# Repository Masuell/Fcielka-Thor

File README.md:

# Fcielka-Thor

This repository contains programms which were used for diploma thesis about [Varroa Destructor detection on honey bees with using narrow spectra of illumination](https://www.vut.cz/studenti/zav-prace/detail/167591).

The thesis focuses on the development of a system for detecting mites on bees using computer vision techniques and illumination with specific wavelengths. The wavelengths employed are 500 nm, corresponding to turquoise light, and 780 nm, corresponding to infrared light. Both classical image processing methods and deep learning approaches are utilized. The primary objective was to capture images of bees as they pass through a [Bee Health Monitor device](https://github.com/boortel/Bee-Health-Monitor) while being illuminated with a narrow spectrum of light. Another goal was to train models capable of reliably identifying mites on bees, thereby reducing the need for manual hive inspections. The developed models include the YOLOv11 object detection architecture and the U-net semantic segmentation architecture, both of which achieved satisfactory performance. A key remaining challenge is the accurate detection of mites located on the edges of bees, which may be addressed by simultaneous illumination with both wavelengths.

You can find [the created dataset here](https://www.kaggle.com/datasets/masuel/bee-hyperspectral-dataset). It consists of photos of bees, mites and bees with mites before and after fumigation treatment. All categories is illuminated by IR, turquoise or white light. Besides that, there is also annotation for semantic segmentation (1 color channel = 1 category) and object detector (YOLO format) there. 

In Best_illumination_ratio folder is code to determine the best illumination ratio (if both colors are turned on).

In CameraCalibration folder is Calibrator module for Bee Health Monitor device.

ImitationOfBothColorsIllumination folder is code to simulate photos with both illumination. The pictures are composed of photos under IR and turquoise with linear regression.

As detection models were used [U-net semantic segmentation architecture](https://github.com/milesial/Pytorch-UNet) and [YOLOv11](https://github.com/ultralytics/ultralytics) object detection architecture.

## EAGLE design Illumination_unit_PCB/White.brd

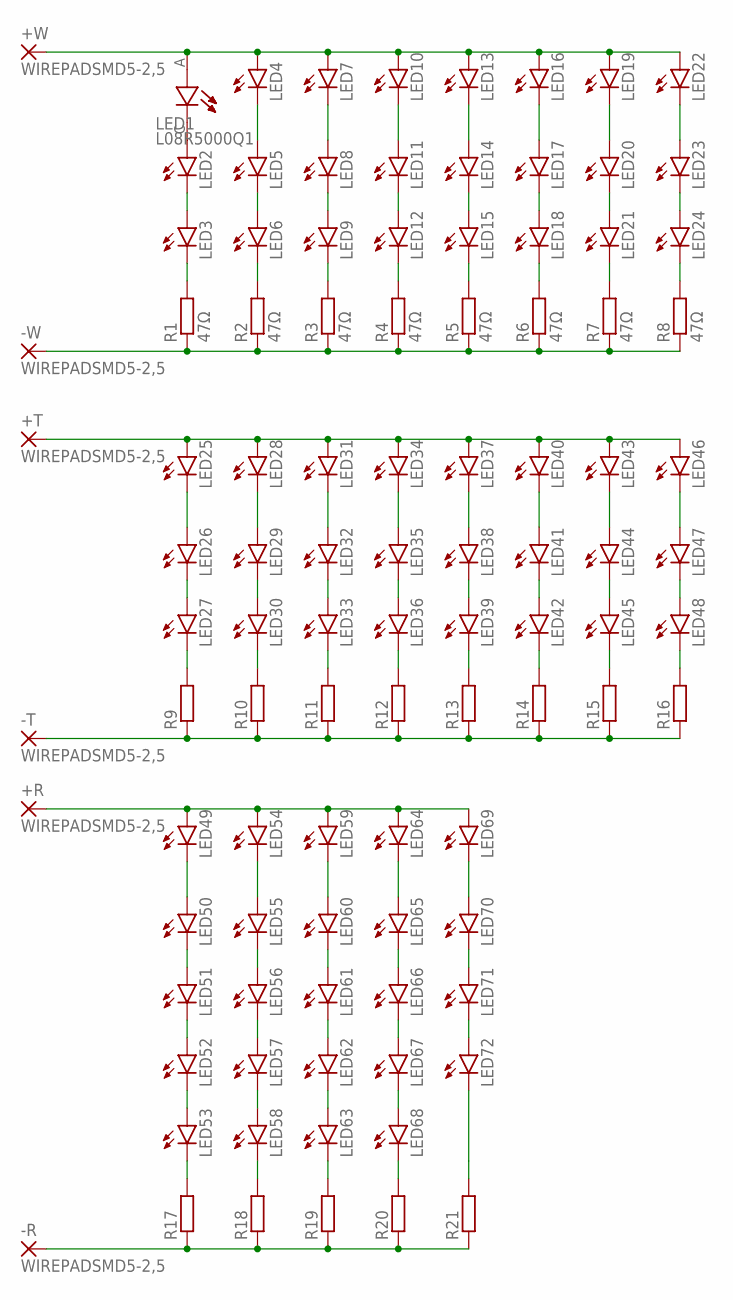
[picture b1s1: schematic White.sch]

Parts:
+R: WIREPADSMD5-2,5; 5-2,5
+T: WIREPADSMD5-2,5; 5-2,5
+W: WIREPADSMD5-2,5; 5-2,5
-R: WIREPADSMD5-2,5; 5-2,5
-T: WIREPADSMD5-2,5; 5-2,5
-W: WIREPADSMD5-2,5; 5-2,5
LED1: L08R5000Q1; LEDRD254W57D500H1070
LED2, LED3, LED4, LED5, LED6, LED7, LED8, LED9, LED10, LED11, LED12, LED13, LED14, LED15, LED16, LED17, LED18, LED19, LED20, LED21, LED22, LED23, LED24, LED25, LED26, LED27, LED28, LED29, LED30, LED31, LED32, LED33, LED34, LED35, LED36, LED37, LED38, LED39, LED40, LED41, LED42, LED43, LED44, LED45, LED46, LED47, LED48, LED49, LED50, LED51, LED52, LED53, LED54, LED55, LED56, LED57, LED58, LED59, LED60, LED61, LED62, LED63, LED64, LED65, LED66, LED67, LED68, LED69, LED70, LED71, LED72: LED5MM
R1, R2, R3, R4, R5, R6, R7, R8: 47Ω; 0411/15
R9, R10, R11, R12, R13, R14, R15, R16, R17, R18, R19, R20, R21: R-EU_0207/12; 0207/12

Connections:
unnamed: LED1.C, LED2.A
unnamed: LED2.K (C), LED3.A
unnamed: LED3.K (C), R1.2
unnamed: +W.1, LED1.A, LED4.A, LED7.A, LED10.A, LED13.A, LED16.A, LED19.A, LED22.A
unnamed: LED25.K (C), LED26.A
unnamed: LED4.K (C), LED5.A
unnamed: LED5.K (C), LED6.A
unnamed: LED6.K (C), R2.2
unnamed: LED7.K (C), LED8.A
unnamed: LED8.K (C), LED9.A
unnamed: LED9.K (C), R3.2
unnamed: LED10.K (C), LED11.A
unnamed: LED11.K (C), LED12.A
unnamed: LED12.K (C), R4.2
unnamed: LED22.K (C), LED23.A
unnamed: LED13.K (C), LED14.A
unnamed: LED14.K (C), LED15.A
unnamed: LED15.K (C), R5.2
unnamed: LED16.K (C), LED17.A
unnamed: LED17.K (C), LED18.A
unnamed: LED18.K (C), R6.2
unnamed: LED19.K (C), LED20.A
unnamed: LED20.K (C), LED21.A
unnamed: LED21.K (C), R7.2
unnamed: LED23.K (C), LED24.A
unnamed: LED24.K (C), R8.2
unnamed: LED26.K (C), LED27.A
unnamed: LED27.K (C), R9.2
unnamed: +T.1, LED25.A, LED28.A, LED31.A, LED34.A, LED37.A, LED40.A, LED43.A, LED46.A
unnamed: LED28.K (C), LED29.A
unnamed: LED29.K (C), LED30.A
unnamed: LED30.K (C), R10.2
unnamed: LED31.K (C), LED32.A
unnamed: LED32.K (C), LED33.A
unnamed: -W.1, R1.1, R2.1, R3.1, R4.1, R5.1, R6.1, R7.1, R8.1
unnamed: LED33.K (C), R11.2
unnamed: LED34.K (C), LED35.A
unnamed: LED35.K (C), LED36.A
unnamed: LED36.K (C), R12.2
unnamed: LED37.K (C), LED38.A
unnamed: LED38.K (C), LED39.A
unnamed: LED39.K (C), R13.2
unnamed: LED40.K (C), LED41.A
unnamed: LED41.K (C), LED42.A
unnamed: LED42.K (C), R14.2
unnamed: LED43.K (C), LED44.A
unnamed: LED44.K (C), LED45.A
unnamed: LED45.K (C), R15.2
unnamed: -T.1, R9.1, R10.1, R11.1, R12.1, R13.1, R14.1, R15.1, R16.1
unnamed: LED46.K (C), LED47.A
unnamed: LED47.K (C), LED48.A
unnamed: LED48.K (C), R16.2
unnamed: LED49.K (C), LED50.A
unnamed: LED50.K (C), LED51.A
unnamed: LED51.K (C), LED52.A
unnamed: +R.1, LED49.A, LED54.A, LED59.A, LED64.A, LED69.A
unnamed: -R.1, R17.1, R18.1, R19.1, R20.1, R21.1
unnamed: LED52.K (C), LED53.A
unnamed: LED53.K (C), R17.2
unnamed: LED54.K (C), LED55.A
unnamed: LED55.K (C), LED56.A
unnamed: LED56.K (C), LED57.A
unnamed: LED57.K (C), LED58.A
unnamed: LED58.K (C), R18.2
unnamed: LED59.K (C), LED60.A
unnamed: LED60.K (C), LED61.A
unnamed: LED61.K (C), LED62.A
unnamed: LED62.K (C), LED63.A
unnamed: LED63.K (C), R19.2
unnamed: LED64.K (C), LED65.A
unnamed: LED65.K (C), LED66.A
unnamed: LED66.K (C), LED67.A
unnamed: LED67.K (C), LED68.A
unnamed: LED68.K (C), R20.2
unnamed: LED69.K (C), LED70.A
unnamed: LED70.K (C), LED71.A
unnamed: LED71.K (C), LED72.A
unnamed: LED72.K (C), R21.2

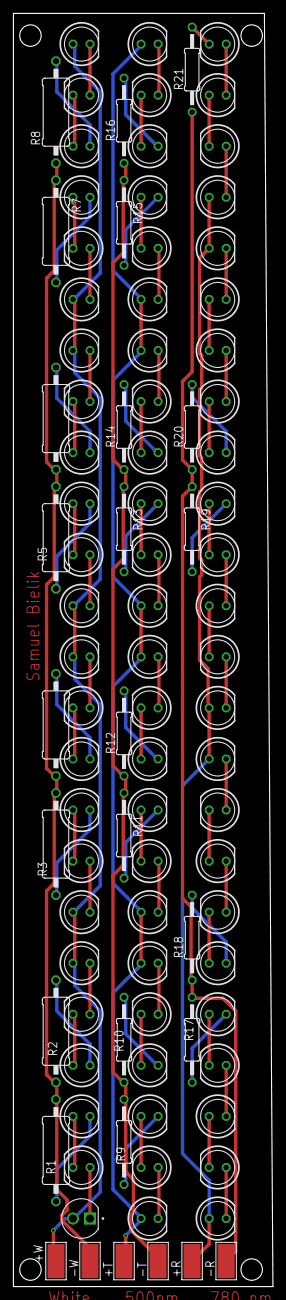
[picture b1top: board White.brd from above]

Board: 2 copper layers, 38.7 x 190.0 mm, 99 parts (0 on the bottom side), 78 nets.
